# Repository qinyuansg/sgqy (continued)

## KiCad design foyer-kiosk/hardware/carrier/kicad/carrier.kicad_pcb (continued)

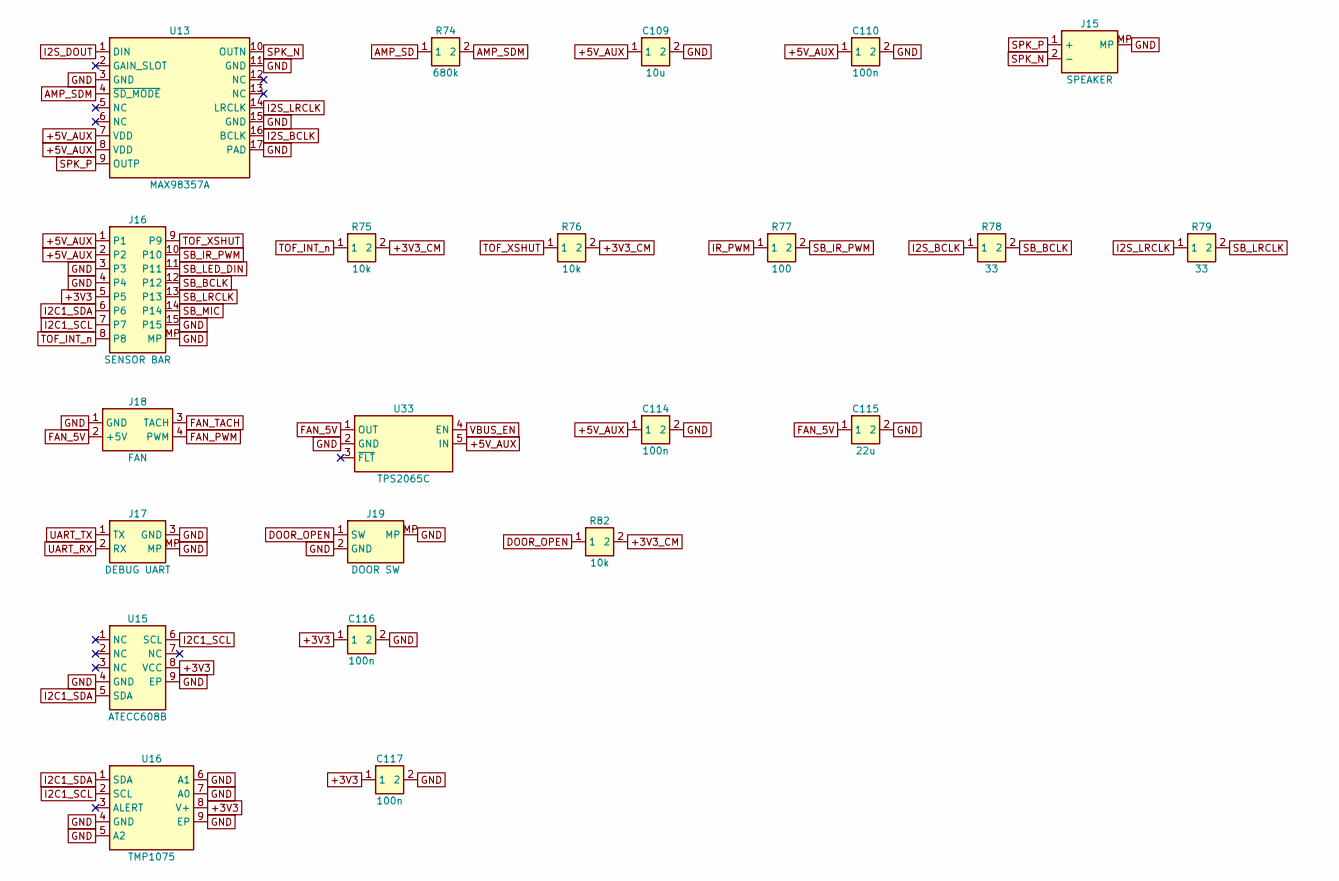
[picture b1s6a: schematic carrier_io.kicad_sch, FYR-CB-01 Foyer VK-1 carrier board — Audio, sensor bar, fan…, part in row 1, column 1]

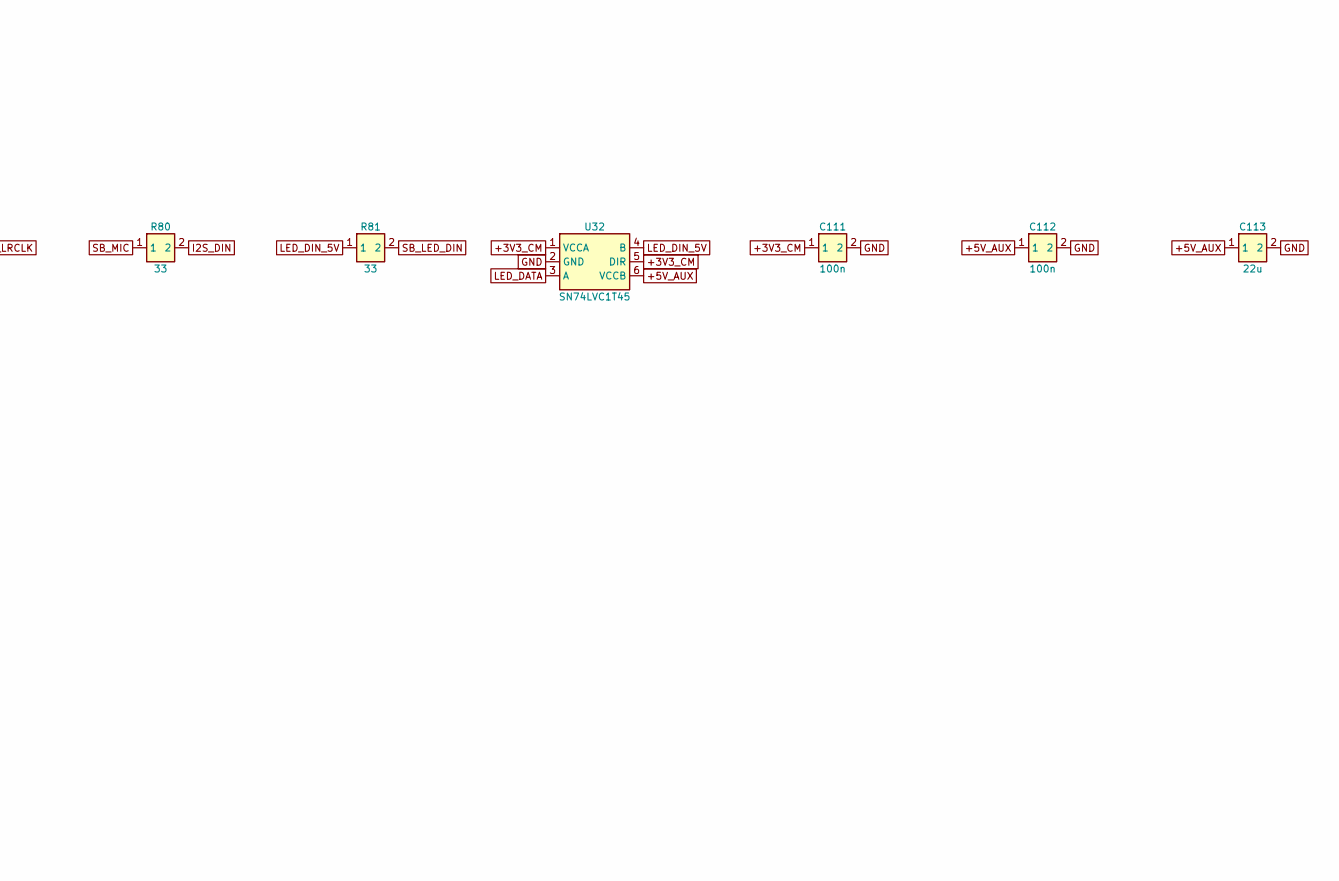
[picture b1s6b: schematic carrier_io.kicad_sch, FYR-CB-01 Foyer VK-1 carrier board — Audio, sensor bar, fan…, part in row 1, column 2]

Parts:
C109: 10u; C_0805_2012Metric
C110, C111, C112, C114, C116, C117: 100n; C_0402_1005Metric
C113, C115: 22u; C_0805_2012Metric
J15: SPEAKER; JST_PH_S2B-PH-SM4-TB_1x02-1MP_P2.00mm_Horizontal; MPN S2B-PH-SM4-TB
J16: SENSOR BAR; JST_GH_SM15B-GHS-TB_1x15-1MP_P1.25mm_Horizontal; MPN SM15B-GHS-TB
J17: DEBUG UART; JST_GH_SM03B-GHS-TB_1x03-1MP_P1.25mm_Horizontal; MPN SM03B-GHS-TB
J18: FAN; PinHeader_1x04_P2.54mm_Vertical; MPN 22-28-4043
J19: DOOR SW; JST_GH_SM02B-GHS-TB_1x02-1MP_P1.25mm_Horizontal; MPN SM02B-GHS-TB
R74: 680k; R_0402_1005Metric
R75, R76, R82: 10k; R_0402_1005Metric
R77: 100; R_0402_1005Metric
R78, R79, R80, R81: 33; R_0402_1005Metric
U13: MAX98357A; TQFN-16-1EP_3x3mm_P0.5mm_EP1.23x1.23mm; MPN MAX98357AETE+T
U15: ATECC608B; DFN-8-1EP_3x2mm_P0.5mm_EP1.3x1.5mm; MPN ATECC608B-MAHDA-T
U16: TMP1075; WSON-8-1EP_2x2mm_P0.5mm_EP0.9x1.6mm_ThermalVias; MPN TMP1075DSGR
U32: SN74LVC1T45; SOT-23-6; MPN SN74LVC1T45DBVR
U33: TPS2065C; SOT-23-5; MPN TPS2065CDBVR

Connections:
+3V3: C116.1, C117.1, J16.5, U15.8 (VCC), U16.8 (V+); also elsewhere on the board
+3V3_CM: C111.1, R75.2, R76.2, R82.2, U32.1 (VCCA), U32.5 (DIR); also elsewhere on the board
+5V_AUX: C109.1, C110.1, C112.1, C113.1, C114.1, J16.1, J16.2, U13.7 (VDD), U13.8 (VDD), U32.6 (VCCB), U33.5 (IN); also elsewhere on the board
AMP_SD: R74.1; also elsewhere on the board
AMP_SDM: R74.2, U13.4 (~SD_MODE)
DOOR_OPEN: J19.1 (SW), R82.1; also elsewhere on the board
FAN_5V: C115.1, J18.2 (+5V), U33.1 (OUT)
FAN_PWM: J18.4 (PWM); also elsewhere on the board
FAN_TACH: J18.3 (TACH); also elsewhere on the board
GND: C109.2, C110.2, C111.2, C112.2, C113.2, C114.2, C115.2, C116.2, C117.2, J15.MP, J16.3, J16.4, J16.15, J16.MP, J17.3 (GND), J17.MP, J18.1 (GND), J19.2 (GND), J19.MP, U13.3 (GND), U13.11 (GND), U13.15 (GND), U13.17 (PAD), U15.4 (GND), U15.9 (EP), U16.4 (GND), U16.5 (A2), U16.6 (A1), U16.7 (A0), U16.9 (EP), U32.2 (GND), U33.2 (GND); also elsewhere on the board
I2C1_SCL: J16.7, U15.6 (SCL), U16.2 (SCL); also elsewhere on the board
I2C1_SDA: J16.6, U15.5 (SDA), U16.1 (SDA); also elsewhere on the board
I2S_BCLK: R78.1, U13.16 (BCLK); also elsewhere on the board
I2S_DIN: R80.2; also elsewhere on the board
I2S_DOUT: U13.1 (DIN); also elsewhere on the board
I2S_LRCLK: R79.1, U13.14 (LRCLK); also elsewhere on the board
IR_PWM: R77.1; also elsewhere on the board
LED_DATA: U32.3 (A); also elsewhere on the board
LED_DIN_5V: R81.1, U32.4 (B)
SB_BCLK: J16.12, R78.2
SB_IR_PWM: J16.10, R77.2
SB_LED_DIN: J16.11, R81.2
SB_LRCLK: J16.13, R79.2
SB_MIC: J16.14, R80.1
SPK_N: J15.2 (-), U13.10 (OUTN)
SPK_P: J15.1 (+), U13.9 (OUTP)
TOF_INT_n: J16.8, R75.1; also elsewhere on the board
TOF_XSHUT: J16.9, R76.1; also elsewhere on the board
UART_RX: J17.2 (RX); also elsewhere on the board
UART_TX: J17.1 (TX); also elsewhere on the board
VBUS_EN: U33.4 (EN); also elsewhere on the board

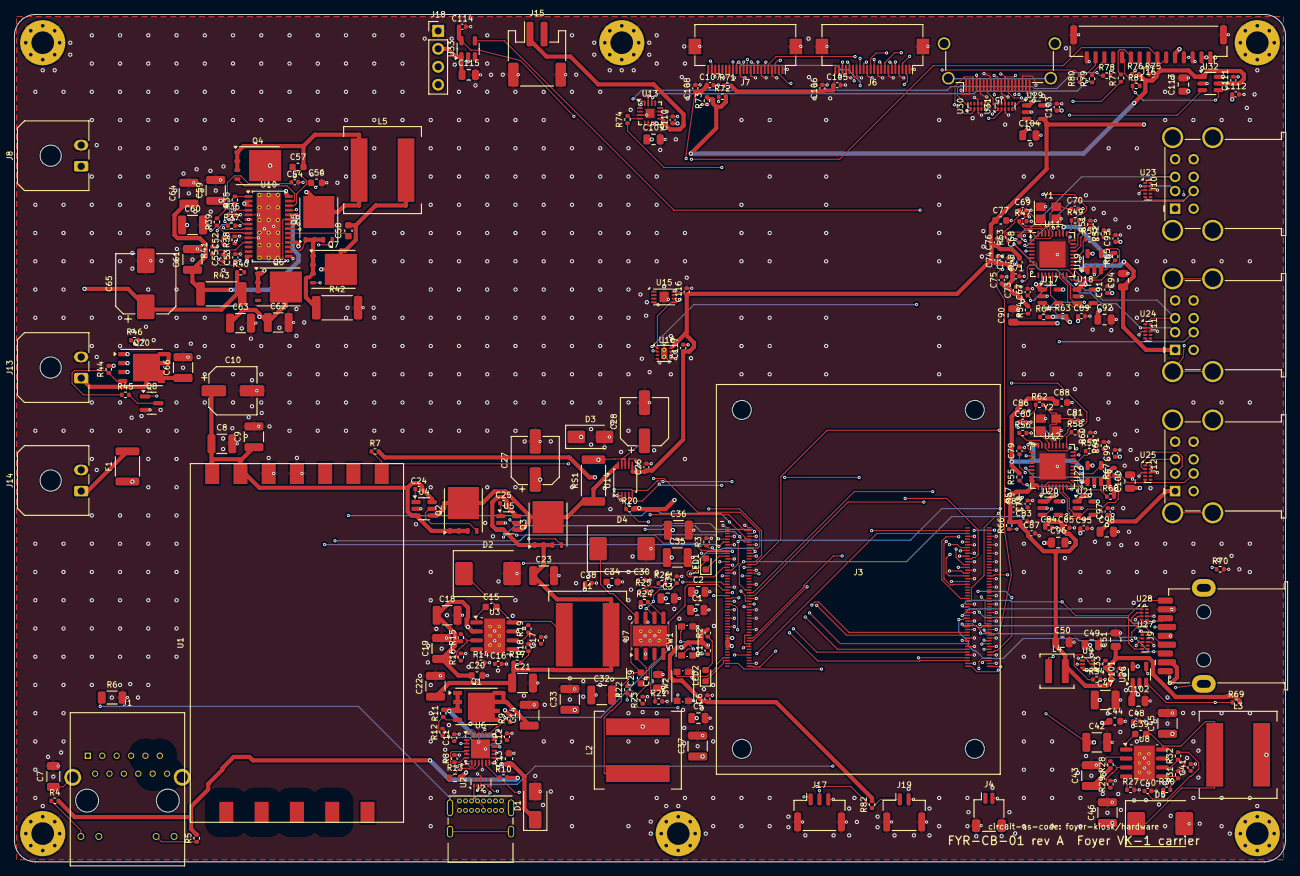
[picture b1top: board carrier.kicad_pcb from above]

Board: 6 copper layers, 180.0 x 120.0 mm, 284 parts (0 on the bottom side), 235 nets.

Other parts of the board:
H1, H2, H3, H4, H5, H6: MountingHole_3.2mm_M3_Pad_Via

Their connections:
GND: H1.1, H2.1, H3.1, H4.1, H5.1, H6.1; also elsewhere on the board

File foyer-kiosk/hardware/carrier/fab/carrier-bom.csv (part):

Designators,Qty,Value,Description,Manufacturer,MPN,Footprint,DNP,Provisional
"C1,C2,C3,C49,C109",5,10u,Capacitor 10u 10V X7R 0805,Any (to spec),,C_0805_2012Metric,,
"C4,C5",2,100n,Capacitor 100n 10V X7R 0805,Any (to spec),,C_0805_2012Metric,,
"C6,C11,C12,C105,C107",5,1u,Capacitor 1u 16V X7R 0402,Any (to spec),,C_0402_1005Metric,,
C7,1,1n,Capacitor 1nF 2kV X7R 1206 (chassis bond),Any (to spec),,C_1206_3216Metric,,
"C8,C9,C21,C22,C23",5,22u,Capacitor 22u 25V X7R 1210,Any (to spec),,C_1210_3225Metric,,
"C10,C27,C28",3,100u,Hybrid polymer 100uF 25V 6.3x7.7,Panasonic,EEH-ZA1E101XP,CP_Elec_6.3x7.7,,
C13,1,1u,Capacitor 1u 50V X7R 0603,Any (to spec),,C_0603_1608Metric,,
"C14,C18,C19,C61,C62,C63,C64",7,10u,Capacitor 10u 50V X7R 1210,Any (to spec),,C_1210_3225Metric,,
"C15,C29,C34,C39,C44,C57",6,100n,Capacitor 100n 25V X7R 0603,Any (to spec),,C_0603_1608Metric,,
"C16,C30,C40",3,5.6n,Capacitor 5.6n 25V X7R 0402,Any (to spec),,C_0402_1005Metric,,
"C17,C31,C41",3,56p,Capacitor 56p 25V C0G 0402,Any (to spec),,C_0402_1005Metric,,
"C20,C58",2,100n,Capacitor 100n 50V X7R 0603,Any (to spec),,C_0603_1608Metric,,
"C24,C25,C53",3,100n,Capacitor 100n 25V X7R 0402,Any (to spec),,C_0402_1005Metric,,
"C26,C38,C48,C71,C72,C73,C74,C75,C76,C82,C83,C84,C85,C86,C87,C106,C108,C110,C111,C112,C116,C117",22,100n,Capacitor 100n 16V X7R 0402,Any (to spec),,C_0402_1005Metric,,
"C32,C33,C42,C43,C59,C60,C66",7,10u,Capacitor 10u 25V X7R 1210,Any (to spec),,C_1210_3225Metric,,
"C35,C36,C37,C45,C46,C47",6,47u,Capacitor 47u 10V X7R 1210,Any (to spec),,C_1210_3225Metric,,
"C50,C51",2,22u,Capacitor 22u 6.3V X7R 0805,Any (to spec),,C_0805_2012Metric,,
C52,1,330p,Capacitor 330p 25V C0G 0402,Any (to spec),,C_0402_1005Metric,,
C54,1,33n,Capacitor 33n 25V X7R 0402,Any (to spec),,C_0402_1005Metric,,
C55,1,470p,Capacitor 470p 25V C0G 0402,Any (to spec),,C_0402_1005Metric,,
C56,1,4.7u,Capacitor 4.7u 16V X7R 0603,Any (to spec),,C_0603_1608Metric,,
C65,1,100u,Hybrid polymer 100uF 35V 8x10,Panasonic,EEH-ZA1V101P,CP_Elec_8x10,,
"C67,C68,C78,C79",4,1u,Capacitor 1u X7R 0402,Any (to spec),,C_0402_1005Metric,,
"C69,C70,C80,C81",4,27p,Capacitor 27p C0G 0402,Any (to spec),,C_0402_1005Metric,,
"C77,C88",2,4.7u,Capacitor 4.7u 10V X7R 0603,Any (to spec),,C_0603_1608Metric,,
"C89,C91,C93,C95,C97,C99,C101,C103,C114",9,100n,Capacitor 100n X7R 0402,Any (to spec),,C_0402_1005Metric,,
"C90,C92,C94,C96,C98,C100,C102,C104,C113,C115",10,22u,Capacitor 22u 10V X7R 0805,Any (to spec),,C_0805_2012Metric,,
D1,1,SMAJ22A,"TVS 22 V standoff, VBUS clamp",Littelfuse,SMAJ22A,D_SMA,,
"D2,D4,D5",3,B560C,Schottky 60 V 5 A SMC (catch diode),Diodes Inc,B560C-13-F,D_SMC,,
D3,1,SMAJ15A,"TVS 15 V standoff, 12 V bus clamp",Littelfuse,SMAJ15A,D_SMA,,
F1,1,1.5A,PTC resettable fuse 1.5 A hold 24 V 1812,Bourns,MF-MSMF150/24X-2,Fuse_1812_4532Metric,,
J1,1,RJ45 PoE++,"RJ45 MagJack 1000BASE-T, 4PPoE 100 W, LEDs, tab up",Bel Fuse,0826-1X1T-HS-F,Bel_0826-1X1T-HS-F_PROVISIONAL,,Footprint and PoE tap pin assignment must be checked against the Bel drawing
J2,1,USB-C,USB-C receptacle (PD power in + rpiboot service),GCT,USB4085-GF-A,USB_C_Receptacle_GCT_USB4085,,
J3,1,CM5 socket,"CM5 board-to-board receptacle pair (2 pcs per board), 1.5 mm stack",Hirose,DF40C-100DS-0.4V(51),RPi_CM5_DF40C-100DS_Pair,,
J4,1,RTC,RTC battery connector (Raspberry Pi RTC battery SC1191),JST,SM02B-SRSS-TB,JST_SH_SM02B-SRSS-TB_1x02-1MP_P1.00mm_Horizontal,,
J5,1,HDMI,"HDMI type-A receptacle, right angle (display)",Amphenol,10029449-111RLF,HDMI_A_Amphenol_10029449-x01xLF_Horizontal,,
J6,1,CAM0,"22-pin 0.5 mm FPC, camera 0 (Raspberry Pi CM camera pinout)",Hirose,FH12-22S-0.5SH(55),Hirose_FH12-22S-0.5SH_1x22-1MP_P0.50mm_Horizontal,,
J7,1,CAM1,"22-pin 0.5 mm FPC, camera 1 (Raspberry Pi CM camera pinout)",Hirose,FH12-22S-0.5SH(55),Hirose_FH12-22S-0.5SH_1x22-1MP_P0.50mm_Horizontal,,
J8,1,PRINTER 24V,"Printer power out (24 V, 3 A)",Molex,43650-0200,Molex_Micro-Fit_3.0_43650-0200_1x02_P3.00mm_Horizontal,,
J9,1,USB3 reader,USB 3.0 type-A receptacle (passport/ID reader),Würth Elektronik,692122030100,USB3_A_Receptacle_Wuerth_692122030100,,
J10,1,USB touch|scanner,USB 2.0 type-A dual stacked receptacle,Würth Elektronik,61400826021,USB_A_Wuerth_61400826021_Horizontal_Stacked,,
J11,1,USB printer|NFC,USB 2.0 type-A dual stacked receptacle,Würth Elektronik,61400826021,USB_A_Wuerth_61400826021_Horizontal_Stacked,,
J12,1,USB LTE|service,USB 2.0 type-A dual stacked receptacle,Würth Elektronik,61400826021,USB_A_Wuerth_61400826021_Horizontal_Stacked,,
J13,1,DISPLAY 12V,Display power out (12 V),Molex,43650-0200,Molex_Micro-Fit_3.0_43650-0200_1x02_P3.00mm_Horizontal,,
J14,1,AUX 12V,Aux 12 V out (reader),Molex,43650-0200,Molex_Micro-Fit_3.0_43650-0200_1x02_P3.00mm_Horizontal,,
J15,1,SPEAKER,"Speaker header (4–8 Ω, 3 W)",JST,S2B-PH-SM4-TB,JST_PH_S2B-PH-SM4-TB_1x02-1MP_P2.00mm_Horizontal,,
J16,1,SENSOR BAR,Sensor bar cable (15-pin GH),JST,SM15B-GHS-TB,JST_GH_SM15B-GHS-TB_1x15-1MP_P1.25mm_Horizontal,,
J17,1,DEBUG UART,"Service console (3.3 V UART, Raspberry Pi Debug Probe pinout)",JST,SM03B-GHS-TB,JST_GH_SM03B-GHS-TB_1x03-1MP_P1.25mm_Horizontal,,
J18,1,FAN,4-pin PWM fan header 2.54 mm,Molex,22-28-4043,PinHeader_1x04_P2.54mm_Vertical,,
J19,1,DOOR SW,Service-door switch (closed = door shut),JST,SM02B-GHS-TB,JST_GH_SM02B-GHS-TB_1x02-1MP_P1.25mm_Horizontal,,
L1,1,10uH,Power inductor 10uH shielded,Coilcraft,XAL1010-103MEB,L_Coilcraft_XAL1010-XXX,,
"L2,L3",2,6.8uH,Power inductor 6.8uH shielded,Coilcraft,XAL1010-682MEB,L_Coilcraft_XAL1010-XXX,,
L4,1,1uH,Power inductor 1 µH,Coilcraft,XAL4020-102MEB,L_Coilcraft_XAL4020-XXX,,
L5,1,10uH,"Power inductor 10 µH, Isat > 14 A",Coilcraft,XAL1010-103MEB,L_Coilcraft_XAL1010-XXX,,
LED1,1,green,LED green 0603 (CM5 activity),Lite-On,LTST-C191KGKT,LED_0603_1608Metric,,
LED2,1,red,LED red 0603 (CM5 power),Lite-On,LTST-C191KRKT,LED_0603_1608Metric,,
Q1,1,Si7461DP,P-MOSFET -60 V PowerPAK SO-8 (USB-C VBUS switch),Vishay,SI7461DP-T1-GE3,PowerPAK_SO-8_Single,,
"Q2,Q3,Q4,Q5,Q6,Q7",6,BSC093N04LS,N-MOSFET 40 V 9.3 mΩ SuperSO8,Infineon,BSC093N04LSGATMA1,TDSON-8-1,,
Q8,1,2N7002,N-MOSFET 60 V SOT-23,onsemi,2N7002LT1G,SOT-23,,
Q20,1,Si7461DP,P-MOSFET -60 V PowerPAK SO-8 (display switch),Vishay,SI7461DP-T1-GE3,PowerPAK_SO-8_Single,,
"R1,R2,R4,R5",4,330,Resistor 330 1% 0402,Any (to spec),,R_0402_1005Metric,,
R3,1,10k,Resistor 10k 0402 — fit after provisioning to write-protect the boot EEPROM,Any (to spec),,R_0402_1005Metric,DNP,
R6,1,1M,Resistor 1M 1% 1206,Any (to spec),,R_1206_3216Metric,,
"R7,R8,R9,R10,R20,R35,R45,R48,R49,R50,R51,R52,R54,R55,R57,R58,R59,R60,R61,R63,R64,R65,R66,R67,R68,R69,R71,R75,R76,R82",30,10k,Resistor 10k 1% 0402,Any (to spec),,R_0402_1005Metric,,
"R11,R33,R36,R44,R46",5,100k,Resistor 100k 1% 0402,Any (to spec),,R_0402_1005Metric,,
R12,1,1k,Resistor 1k 1% 0402,Any (to spec),,R_0402_1005Metric,,
R13,1,1k,Resistor 1k 1% 0603,Any (to spec),,R_0603_1608Metric,,
"R14,R21,R27",3,243k,Resistor 243k 1% 0402,Any (to spec),,R_0402_1005Metric,,
"R15,R22,R28",3,294k,Resistor 294k 1% 0402,Any (to spec),,R_0402_1005Metric,,
R16,1,28k,Resistor 28k 1% 0402,Any (to spec),,R_0402_1005Metric,,
R17,1,143k,Resistor 143k 1% 0402,Any (to spec),,R_0402_1005Metric,,
"R18,R25,R31",3,10k2,Resistor 10k2 1% 0402,Any (to spec),,R_0402_1005Metric,,
"R19,R26,R32",3,15k4,Resistor 15k4 1% 0402,Any (to spec),,R_0402_1005Metric,,
"R23,R29",2,43k2,Resistor 43k2 1% 0402,Any (to spec),,R_0402_1005Metric,,
"R24,R30",2,53k6,Resistor 53k6 1% 0402,Any (to spec),,R_0402_1005Metric,,
R34,1,22.1k,Resistor 22.1k 1% 0402,Any (to spec),,R_0402_1005Metric,,
R37,1,93k1,Resistor 93k1 1% 0402,Any (to spec),,R_0402_1005Metric,,
R38,1,27k4,Resistor 27k4 1% 0402,Any (to spec),,R_0402_1005Metric,,
R39,1,9k53,Resistor 9k53 1% 0402,Any (to spec),,R_0402_1005Metric,,
R40,1,576k,Resistor 576k 1% 0402,Any (to spec),,R_0402_1005Metric,,
R41,1,20k,Resistor 20k 1% 0402,Any (to spec),,R_0402_1005Metric,,
R42,1,10m,Current sense 10 mΩ 1% 2512 3 W,Vishay Dale,WSLP2512R0100FE,R_2512_6332Metric,,
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
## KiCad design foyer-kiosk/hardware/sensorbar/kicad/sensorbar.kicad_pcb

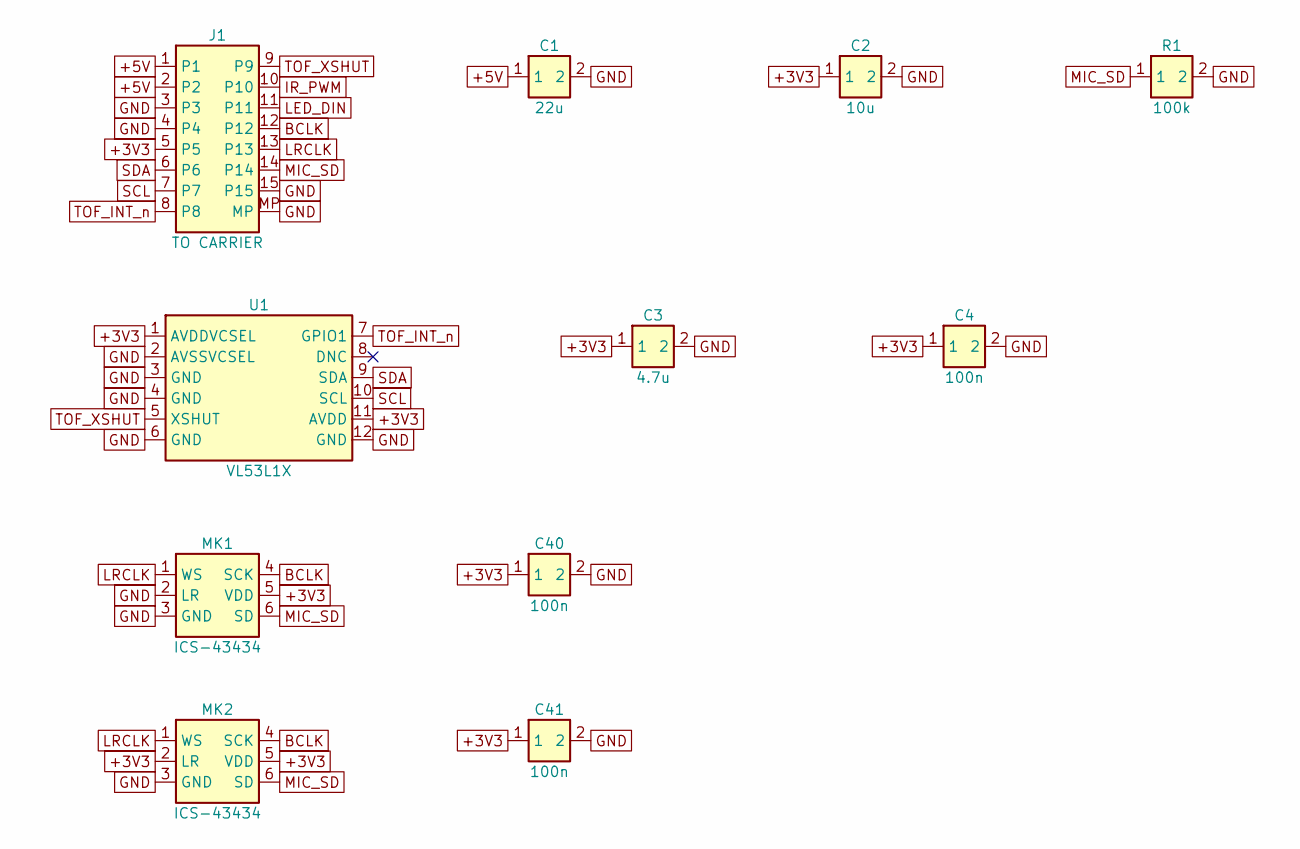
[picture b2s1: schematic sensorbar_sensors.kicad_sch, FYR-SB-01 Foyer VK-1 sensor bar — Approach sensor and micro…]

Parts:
C1: 22u; C_0805_2012Metric
C2: 10u; C_0805_2012Metric
C3: 4.7u; C_0603_1608Metric
C4, C40, C41: 100n; C_0402_1005Metric
J1: TO CARRIER; JST_GH_SM15B-GHS-TB_1x15-1MP_P1.25mm_Horizontal; MPN SM15B-GHS-TB
MK1, MK2: ICS-43434; InvenSense_ICS-43434-6_3.5x2.65mm; MPN ICS-43434
R1: 100k; R_0402_1005Metric
U1: VL53L1X; ST_VL53L1x; MPN VL53L1CXV0FY/1

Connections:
+3V3: C2.1, C3.1, C4.1, C40.1, C41.1, J1.5, MK1.5 (VDD), MK2.2 (LR), MK2.5 (VDD), U1.1 (AVDDVCSEL), U1.11 (AVDD)
+5V: C1.1, J1.1, J1.2; also elsewhere on the board
BCLK: J1.12, MK1.4 (SCK), MK2.4 (SCK)
GND: C1.2, C2.2, C3.2, C4.2, C40.2, C41.2, J1.3, J1.4, J1.15, J1.MP, MK1.2 (LR), MK1.3 (GND), MK2.3 (GND), R1.2, U1.2 (AVSSVCSEL), U1.3 (GND), U1.4 (GND), U1.6 (GND), U1.12 (GND); also elsewhere on the board
IR_PWM: J1.10; also elsewhere on the board
LED_DIN: J1.11; also elsewhere on the board
LRCLK: J1.13, MK1.1 (WS), MK2.1 (WS)
MIC_SD: J1.14, MK1.6 (SD), MK2.6 (SD), R1.1
SCL: J1.7, U1.10 (SCL)
SDA: J1.6, U1.9 (SDA)
TOF_INT_n: J1.8, U1.7 (GPIO1)
TOF_XSHUT: J1.9, U1.5 (XSHUT)

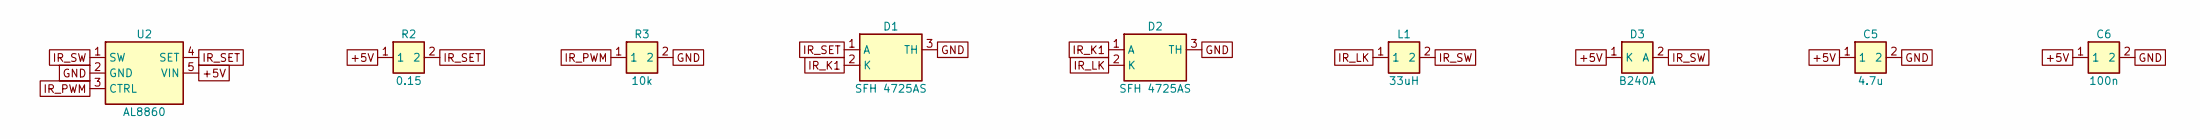
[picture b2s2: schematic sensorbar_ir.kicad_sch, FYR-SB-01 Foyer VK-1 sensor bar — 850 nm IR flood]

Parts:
C5: 4.7u; C_0805_2012Metric
C6: 100n; C_0402_1005Metric
D1, D2: SFH 4725AS; OSRAM_OSLON_Black_SFH4725AS_PROVISIONAL; MPN SFH 4725AS A01
D3: B240A; D_SMA; MPN B240A-13-F
L1: 33uH; L_Coilcraft_XAL5050-XXX; MPN XAL5050-333MEB
R2: 0.15; R_1206_3216Metric; MPN WSL1206R1500FEA
R3: 10k; R_0402_1005Metric
U2: AL8860; TSOT-23-5; MPN AL8860WT-7

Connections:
+5V: C5.1, C6.1, D3.1 (K), R2.1, U2.5 (VIN); also elsewhere on the board
GND: C5.2, C6.2, D1.3 (TH), D2.3 (TH), R3.2, U2.2 (GND); also elsewhere on the board
IR_K1: D1.2 (K), D2.1 (A)
IR_LK: D2.2 (K), L1.1
IR_PWM: R3.1, U2.3 (CTRL); also elsewhere on the board
IR_SET: D1.1 (A), R2.2, U2.4 (SET)
IR_SW: D3.2 (A), L1.2, U2.1 (SW)

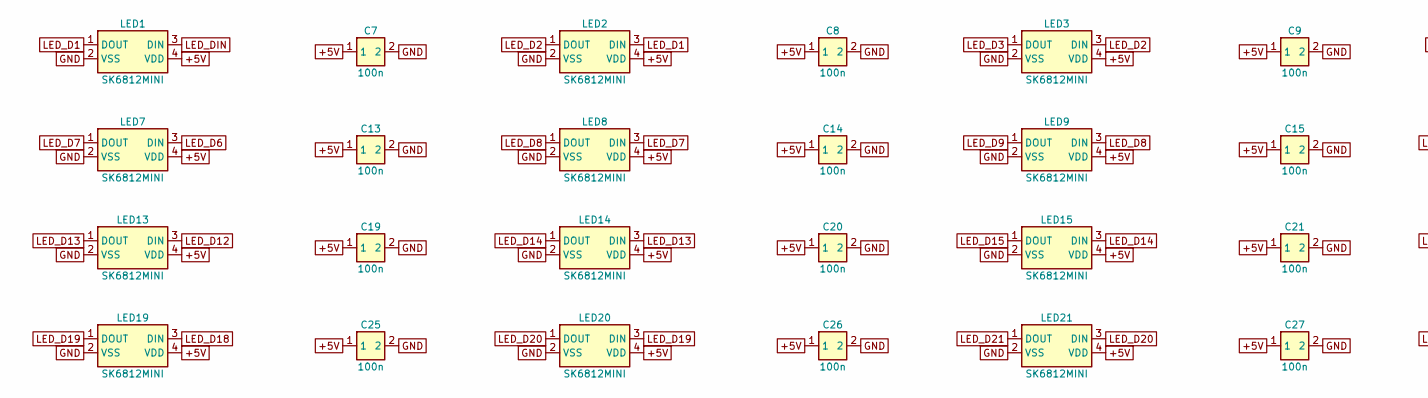
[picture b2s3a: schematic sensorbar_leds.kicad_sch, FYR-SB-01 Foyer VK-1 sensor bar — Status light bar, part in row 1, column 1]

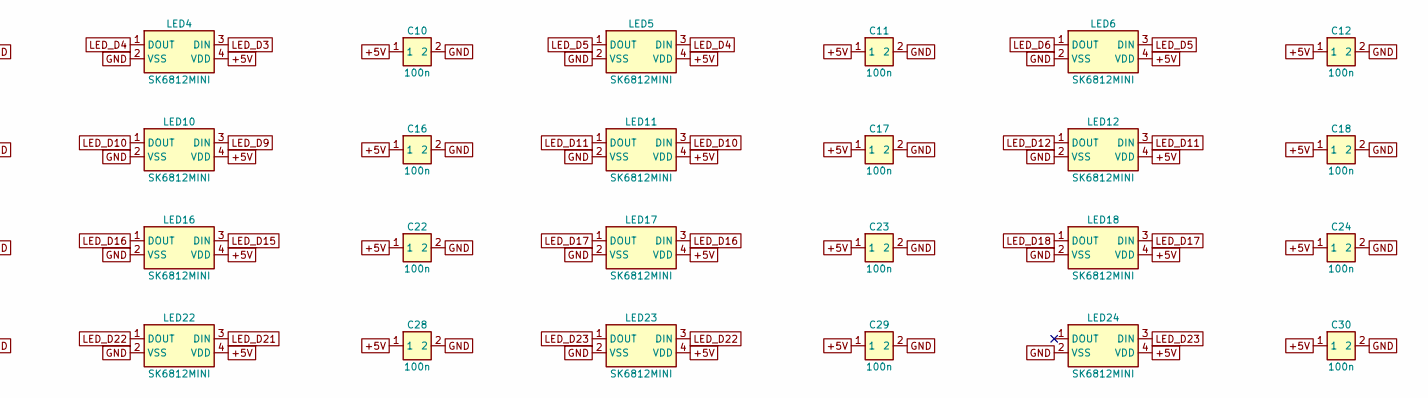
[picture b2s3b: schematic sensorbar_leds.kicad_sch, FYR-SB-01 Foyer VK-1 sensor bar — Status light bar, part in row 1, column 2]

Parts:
C7, C8, C9, C10, C11, C12, C13, C14, C15, C16, C17, C18, C19, C20, C21, C22, C23, C24, C25, C26, C27, C28, C29, C30: 100n; C_0402_1005Metric
LED1, LED2, LED3, LED4, LED5, LED6, LED7, LED8, LED9, LED10, LED11, LED12, LED13, LED14, LED15, LED16, LED17, LED18, LED19, LED20, LED21, LED22, LED23, LED24: SK6812MINI; LED_SK6812MINI_PLCC4_3.5x3.5mm_P1.75mm; MPN SK6812MINI

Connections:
+5V: C7.1, C8.1, C9.1, C10.1, C11.1, C12.1, C13.1, C14.1, C15.1, C16.1, C17.1, C18.1, C19.1, C20.1, C21.1, C22.1, C23.1, C24.1, C25.1, C26.1, C27.1, C28.1, C29.1, C30.1, LED1.4 (VDD), LED2.4 (VDD), LED3.4 (VDD), LED4.4 (VDD), LED5.4 (VDD), LED6.4 (VDD), LED7.4 (VDD), LED8.4 (VDD), LED9.4 (VDD), LED10.4 (VDD), LED11.4 (VDD), LED12.4 (VDD), LED13.4 (VDD), LED14.4 (VDD), LED15.4 (VDD), LED16.4 (VDD), LED17.4 (VDD), LED18.4 (VDD), LED19.4 (VDD), LED20.4 (VDD), LED21.4 (VDD), LED22.4 (VDD), LED23.4 (VDD), LED24.4 (VDD); also elsewhere on the board
GND: C7.2, C8.2, C9.2, C10.2, C11.2, C12.2, C13.2, C14.2, C15.2, C16.2, C17.2, C18.2, C19.2, C20.2, C21.2, C22.2, C23.2, C24.2, C25.2, C26.2, C27.2, C28.2, C29.2, C30.2, LED1.2 (VSS), LED2.2 (VSS), LED3.2 (VSS), LED4.2 (VSS), LED5.2 (VSS), LED6.2 (VSS), LED7.2 (VSS), LED8.2 (VSS), LED9.2 (VSS), LED10.2 (VSS), LED11.2 (VSS), LED12.2 (VSS), LED13.2 (VSS), LED14.2 (VSS), LED15.2 (VSS), LED16.2 (VSS), LED17.2 (VSS), LED18.2 (VSS), LED19.2 (VSS), LED20.2 (VSS), LED21.2 (VSS), LED22.2 (VSS), LED23.2 (VSS), LED24.2 (VSS); also elsewhere on the board
LED_D1: LED1.1 (DOUT), LED2.3 (DIN)
LED_D2: LED2.1 (DOUT), LED3.3 (DIN)
LED_D3: LED3.1 (DOUT), LED4.3 (DIN)
LED_D4: LED4.1 (DOUT), LED5.3 (DIN)
LED_D5: LED5.1 (DOUT), LED6.3 (DIN)
LED_D6: LED6.1 (DOUT), LED7.3 (DIN)
LED_D7: LED7.1 (DOUT), LED8.3 (DIN)
LED_D8: LED8.1 (DOUT), LED9.3 (DIN)
LED_D9: LED9.1 (DOUT), LED10.3 (DIN)
LED_D10: LED10.1 (DOUT), LED11.3 (DIN)
LED_D11: LED11.1 (DOUT), LED12.3 (DIN)
LED_D12: LED12.1 (DOUT), LED13.3 (DIN)
LED_D13: LED13.1 (DOUT), LED14.3 (DIN)
LED_D14: LED14.1 (DOUT), LED15.3 (DIN)
LED_D15: LED15.1 (DOUT), LED16.3 (DIN)
LED_D16: LED16.1 (DOUT), LED17.3 (DIN)
LED_D17: LED17.1 (DOUT), LED18.3 (DIN)
LED_D18: LED18.1 (DOUT), LED19.3 (DIN)
LED_D19: LED19.1 (DOUT), LED20.3 (DIN)
LED_D20: LED20.1 (DOUT), LED21.3 (DIN)
LED_D21: LED21.1 (DOUT), LED22.3 (DIN)
LED_D22: LED22.1 (DOUT), LED23.3 (DIN)
LED_D23: LED23.1 (DOUT), LED24.3 (DIN)
LED_DIN: LED1.3 (DIN); also elsewhere on the board

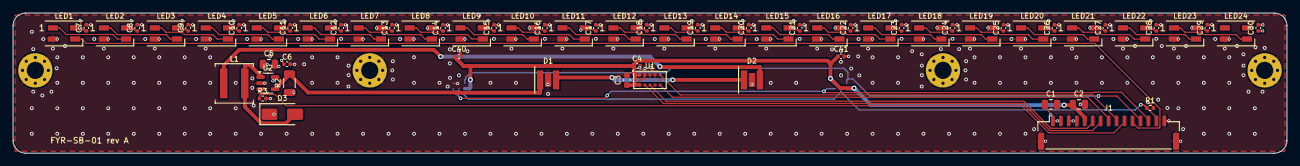
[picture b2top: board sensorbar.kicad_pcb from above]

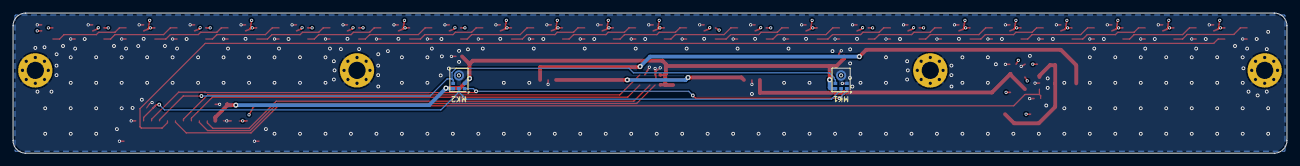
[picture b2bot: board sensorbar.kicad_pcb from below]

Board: 4 copper layers, 200.0 x 22.0 mm, 72 parts (2 on the bottom side), 39 nets.

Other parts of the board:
H1, H2, H3, H4: MountingHole_2.7mm_M2.5_Pad_Via

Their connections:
GND: H1.1, H2.1, H3.1, H4.1; also elsewhere on the board

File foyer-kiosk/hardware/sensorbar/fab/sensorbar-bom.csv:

Designators,Qty,Value,Description,Manufacturer,MPN,Footprint,DNP,Provisional
C1,1,22u,Capacitor 22u 10V X7R 0805,Any (to spec),,C_0805_2012Metric,,
C2,1,10u,Capacitor 10u 10V X7R 0805,Any (to spec),,C_0805_2012Metric,,
C3,1,4.7u,Capacitor 4.7u 10V X7R 0603,Any (to spec),,C_0603_1608Metric,,
"C4,C6,C7,C8,C9,C10,C11,C12,C13,C14,C15,C16,C17,C18,C19,C20,C21,C22,C23,C24,C25,C26,C27,C28,C29,C30,C40,C41",28,100n,Capacitor 100n X7R 0402,Any (to spec),,C_0402_1005Metric,,
C5,1,4.7u,Capacitor 4.7u 10V X7R 0805,Any (to spec),,C_0805_2012Metric,,
"D1,D2",2,SFH 4725AS,"850 nm IR emitter, OSLON Black",ams OSRAM,SFH 4725AS A01,OSRAM_OSLON_Black_SFH4725AS_PROVISIONAL,,Land pattern to be checked against the ams OSRAM drawing
D3,1,B240A,Schottky 40 V 2 A (freewheel),Diodes Inc,B240A-13-F,D_SMA,,
J1,1,TO CARRIER,Cable to carrier J16 (15-pin GH),JST,SM15B-GHS-TB,JST_GH_SM15B-GHS-TB_1x15-1MP_P1.25mm_Horizontal,,
L1,1,33uH,Power inductor 33 µH,Coilcraft,XAL5050-333MEB,L_Coilcraft_XAL5050-XXX,,
"LED1,LED2,LED3,LED4,LED5,LED6,LED7,LED8,LED9,LED10,LED11,LED12,LED13,LED14,LED15,LED16,LED17,LED18,LED19,LED20,LED21,LED22,LED23,LED24",24,SK6812MINI,Addressable RGB LED 3.5x3.5 (status bar),Opsco,SK6812MINI,LED_SK6812MINI_PLCC4_3.5x3.5mm_P1.75mm,,
MK1,1,ICS-43434,"I2S MEMS microphone, bottom port (left channel)",TDK InvenSense,ICS-43434,InvenSense_ICS-43434-6_3.5x2.65mm,,
MK2,1,ICS-43434,"I2S MEMS microphone, bottom port (right channel)",TDK InvenSense,ICS-43434,InvenSense_ICS-43434-6_3.5x2.65mm,,
R1,1,100k,Resistor 100k 0402 (I2S SD bus keeper),Any (to spec),,R_0402_1005Metric,,
R2,1,0.15,Sense 0.15 Ω 1% 1206 (I_LED = 0.1 V / 0.15 Ω ≈ 670 mA),Vishay Dale,WSL1206R1500FEA,R_1206_3216Metric,,
R3,1,10k,Resistor 10k 0402 (IR off by default),Any (to spec),,R_0402_1005Metric,,
U1,1,VL53L1X,"ToF ranging sensor 4 m, I2C @0x29",STMicroelectronics,VL53L1CXV0FY/1,ST_VL53L1x,,
U2,1,AL8860,40 V 1.5 A buck LED driver (IR flood),Diodes Inc,AL8860WT-7,TSOT-23-5,,

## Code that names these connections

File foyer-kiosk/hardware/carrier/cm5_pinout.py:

"""Raspberry Pi CM5 2x100-pin connector map (pin -> signal).

Source: CM5 datasheet (RP-008180-DS) pin table, cross-checked against two independent
open-source CM5 carrier designs derived from the official CM5 IO board (0 differences).
Pins 1-100 = connector J1 (GPIO/Ethernet/power), 101-200 = J2 (high-speed).
"""

CM5_PINS = {
    1: "GND",
    2: "GND",
    3: "ETH_Pair3_P",
    4: "ETH_Pair1_P",
    5: "ETH_Pair3_N",
    6: "ETH_Pair1_N",
    7: "GND",
    8: "GND",
    9: "ETH_Pair2_N",
    10: "ETH_Pair0_N",
    11: "ETH_Pair2_P",
    12: "ETH_Pair0_P",
    13: "GND",
    14: "GND",
    15: "ETH_nLED3",
    16: "FAN_TACHO",
    17: "ETH_nLED2",
    18: "ETH_SYNC_OUT",
    19: "FAN_PWM",
    20: "EEPROM_nWP",
    21: "LED_nACT",
    22: "GND",
    23: "GND",
    24: "GPIO26",
    25: "GPIO21",
    26: "GPIO19",
    27: "GPIO20",
    28: "GPIO13",
    29: "GPIO16",
    30: "GPIO6",
    31: "GPIO12",
    32: "GND",
    33: "GND",
    34: "GPIO5",
    35: "ID_SC",
    36: "ID_SD",
    37: "GPIO7",
    38: "GPIO11",
    39: "GPIO8",
    40: "GPIO9",
    41: "GPIO25",
    42: "GND",
    43: "GND",
    44: "GPIO10",
    45: "GPIO24",
    46: "GPIO22",
    47: "GPIO23",
    48: "GPIO27",
    49: "GPIO18",
    50: "GPIO17",
    51: "GPIO15",
    52: "GND",
    53: "GND",
    54: "GPIO4",
    55: "GPIO14",
    56: "GPIO3",
    57: "SD_CLK",
    58: "GPIO2",
    59: "GND",
    60: "GND",
    61: "SD_DAT3",
    62: "SD_CMD",
    63: "SD_DAT0",
    64: "SD_DAT5",
    65: "GND",
    66: "GND",
    67: "SD_DAT1",
    68: "SD_DAT4",
    69: "SD_DAT2",
    70: "SD_DAT7",
    71: "GND",
    72: "SD_DAT6",
    73: "SD_VDD_Override",
    74: "GND",
    75: "SD_PWR_ON",
    76: "VBAT",
    77: "+5V_IN",
    78: "GPIO_VREF",
    79: "+5V_IN",
    80: "SCL0",
    81: "+5V_IN",
    82: "SDA0",
    83: "+5V_IN",
    84: "+3V3_OUT",
    85: "+5V_IN",
    86: "+3V3_OUT",
    87: "+5V_IN",
    88: "+1V8_OUT",
    89: "WiFi_nDisable",
    90: "+1V8_OUT",
    91: "BT_nDisable",
    92: "PWR_BUT",
    93: "nRPIBOOT",
    94: "CC1",
    95: "LED_nPWR",
    96: "CC2",
    97: "CAM_GPIO0",
    98: "GND",
    99: "PMIC_ENABLE",
    100: "CAM_GPIO1",
    101: "USB_OTG_ID",
    102: "PCIe_nCLKREQ",
    103: "USB2_N",
    104: "PCIE_nWAKE",
    105: "USB2_P",
    106: "PCIE_PWR_EN",
    107: "GND",
    108: "GND",
    109: "PCIe_nRST",
    110: "PCIe_CLK_P",
    111: "VBUS_EN",
    112: "PCIe_CLK_N",
    113: "GND",
    114: "GND",
    115: "MIPI0_D0_N",
    116: "PCIe_RX_P",
    117: "MIPI0_D0_P",
    118: "PCIe_RX_N",
    119: "GND",
    120: "GND",
    121: "MIPI0_D1_N",
    122: "PCIe_TX_P",
    123: "MIPI0_D1_P",
    124: "PCIe_TX_N",
    125: "GND",
    126: "GND",
    127: "MIPI0_C_N",
    128: "USB3_0_RX_N",
    129: "MIPI0_C_P",
    130: "USB3_0_RX_P",
    131: "GND",
    132: "GND",
    133: "MIPI0_D2_N",
    134: "USB3_0_D_P",
    135: "MIPI0_D2_P",
    136: "USB3_0_D_N",
    137: "GND",
    138: "GND",
    139: "MIPI0_D3_N",
    140: "USB3_0_TX_N",
    141: "MIPI0_D3_P",
    142: "USB3_0_TX_P",
    143: "HDMI1_HOTPLUG",
    144: "GND",
    145: "HDMI1_SDA",
    146: "HDMI1_TX2_P",
    147: "HDMI1_SCL",
    148: "HDMI1_TX2_N",
    149: "HDMI1_CEC",
    150: "GND",
    151: "HDMI0_CEC",
    152: "HDMI1_TX1_P",
    153: "HDMI0_HOTPLUG",
    154: "HDMI1_TX1_N",
    155: "GND",
    156: "GND",
    157: "USB3_1_RX_N",
    158: "HDMI1_TX0_P",
    159: "USB3_1_RX_P",
    160: "HDMI1_TX0_N",
    161: "GND",
    162: "GND",
    163: "USB3_1_D_P",
    164: "HDMI1_CLK_P",
    165: "USB3_1_D_N",
    166: "HDMI1_CLK_N",
    167: "GND",
    168: "GND",
    169: "USB3_1_TX_N",
    170: "HDMI0_TX2_P",
    171: "USB3_1_TX_P",
    172: "HDMI0_TX2_N",
    173: "GND",
    174: "GND",
    175: "MIPI1_D0_N",
    176: "HDMI0_TX1_P",
    177: "MIPI1_D0_P",
    178: "HDMI0_TX1_N",
    179: "GND",
    180: "GND",
    181: "MIPI1_D1_N",
    182: "HDMI0_TX0_P",
    183: "MIPI1_D1_P",
    184: "HDMI0_TX0_N",
    185: "GND",
    186: "GND",
    187: "MIPI1_C_N",
    188: "HDMI0_CLK_P",
    189: "MIPI1_C_P",
    190: "HDMI0_CLK_N",
    191: "GND",
    192: "GND",
    193: "MIPI1_D2_N",
    194: "MIPI1_D3_N",
    195: "MIPI1_D2_P",
    196: "MIPI1_D3_P",
    197: "GND",
    198: "GND",
    199: "HDMI0_SDA",
    200: "HDMI0_SCL",
}

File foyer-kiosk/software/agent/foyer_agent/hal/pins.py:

"""GPIO map from foyer-kiosk/hardware/interface-contract.md (rev B, carrier FYR-CB-01).

Only lines the agent drives or watches through libgpiod are listed. Lines
owned by kernel drivers are not: GPIO0/1 (camera 1 I2C), GPIO2/3 (I2C1),
GPIO12 (``IR_PWM``, PWM0), GPIO13 (``LED_DATA``, RP1 PIO) and GPIO18-21 (I2S).
Boot-critical outputs are also set by firmware (``gpio=`` lines in
config.txt) so the display, USB hubs and ToF come up without the agent.
"""

from __future__ import annotations

from dataclasses import dataclass
from enum import Enum


class Direction(Enum):
    IN = "in"
    OUT = "out"


class Edge(Enum):
    NONE = "none"
    RISING = "rising"
    FALLING = "falling"
    BOTH = "both"


@dataclass(frozen=True)
class Pin:
    name: str
    offset: int
    direction: Direction
    initial: int = 0  # outputs: level at request time; inputs: idle level (simulator)
    pull_up: bool = False
    edge: Edge = Edge.NONE
    debounce_ms: int = 0


POE_HIPWR_N = Pin("POE_HIPWR_n", 4, Direction.IN, initial=0, edge=Edge.BOTH, debounce_ms=50)
AMP_SD = Pin("AMP_SD", 5, Direction.OUT, initial=0)
USBC_ATTACH = Pin("USBC_ATTACH", 6, Direction.IN, initial=1, pull_up=True, edge=Edge.BOTH, debounce_ms=50)
PRN_PWR_EN = Pin("PRN_PWR_EN", 16, Direction.OUT, initial=0)
TOF_INT_N = Pin("TOF_INT_n", 17, Direction.IN, initial=1, pull_up=True, edge=Edge.FALLING)
HUB_RESET_N = Pin("HUB_RESET_n", 22, Direction.OUT, initial=1)
DOOR_OPEN = Pin("DOOR_OPEN", 23, Direction.IN, initial=0, pull_up=True, edge=Edge.BOTH, debounce_ms=30)
PD_ALERT_N = Pin("PD_ALERT_n", 24, Direction.IN, initial=1, edge=Edge.FALLING)
PWR_ALERT_N = Pin("PWR_ALERT_n", 25, Direction.IN, initial=1, edge=Edge.BOTH, debounce_ms=10)
DISP_PWR_EN = Pin("DISP_PWR_EN", 26, Direction.OUT, initial=1)
TOF_XSHUT = Pin("TOF_XSHUT", 27, Direction.OUT, initial=1)

ALL_PINS: tuple[Pin, ...] = (
    POE_HIPWR_N,
    AMP_SD,
    USBC_ATTACH,
    PRN_PWR_EN,
    TOF_INT_N,
    HUB_RESET_N,
    DOOR_OPEN,
    PD_ALERT_N,
    PWR_ALERT_N,
    DISP_PWR_EN,
    TOF_XSHUT,
)
